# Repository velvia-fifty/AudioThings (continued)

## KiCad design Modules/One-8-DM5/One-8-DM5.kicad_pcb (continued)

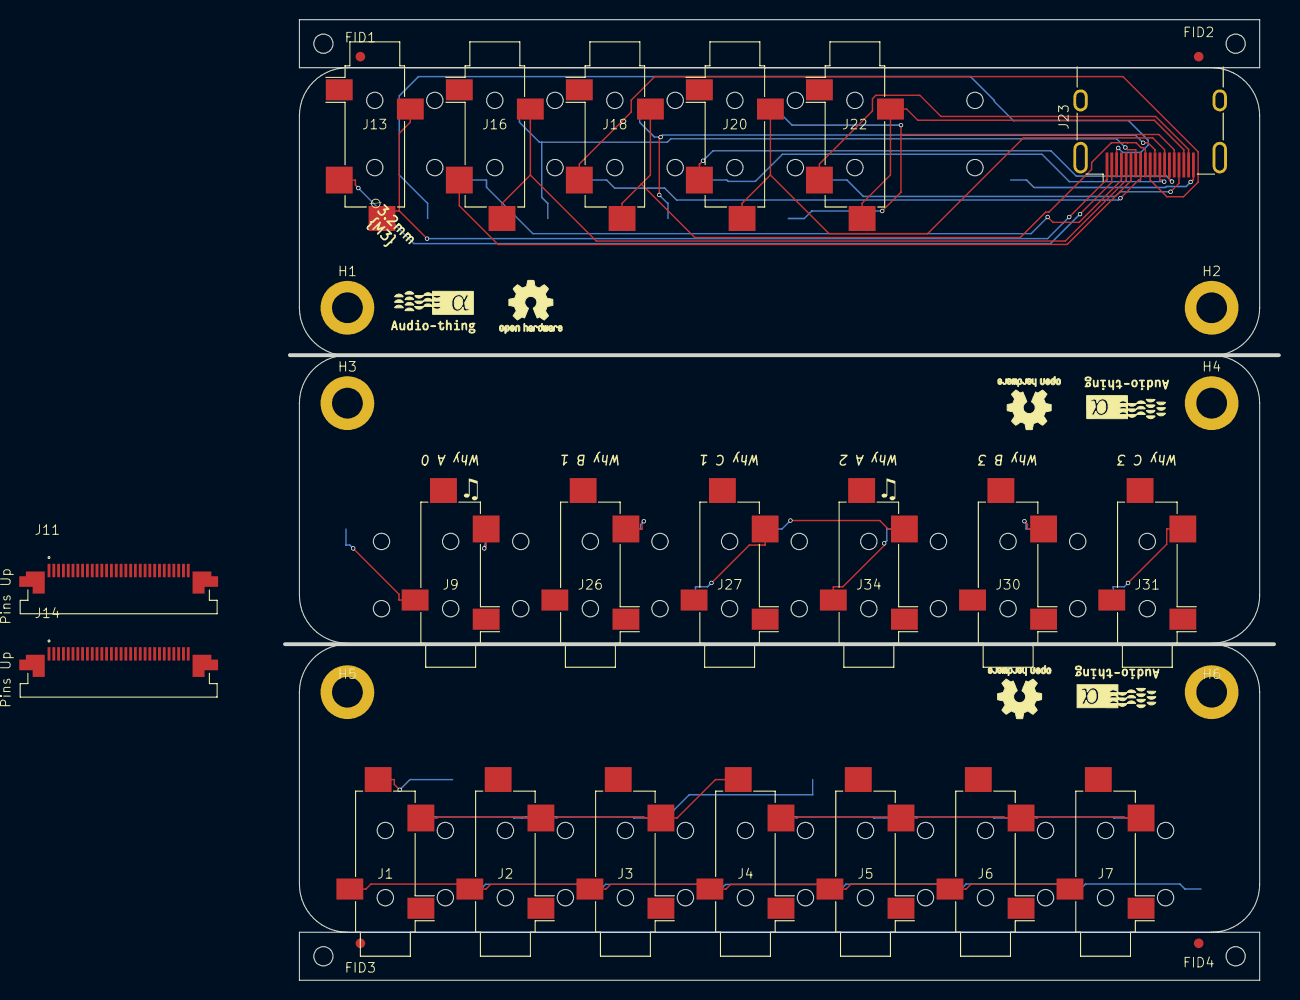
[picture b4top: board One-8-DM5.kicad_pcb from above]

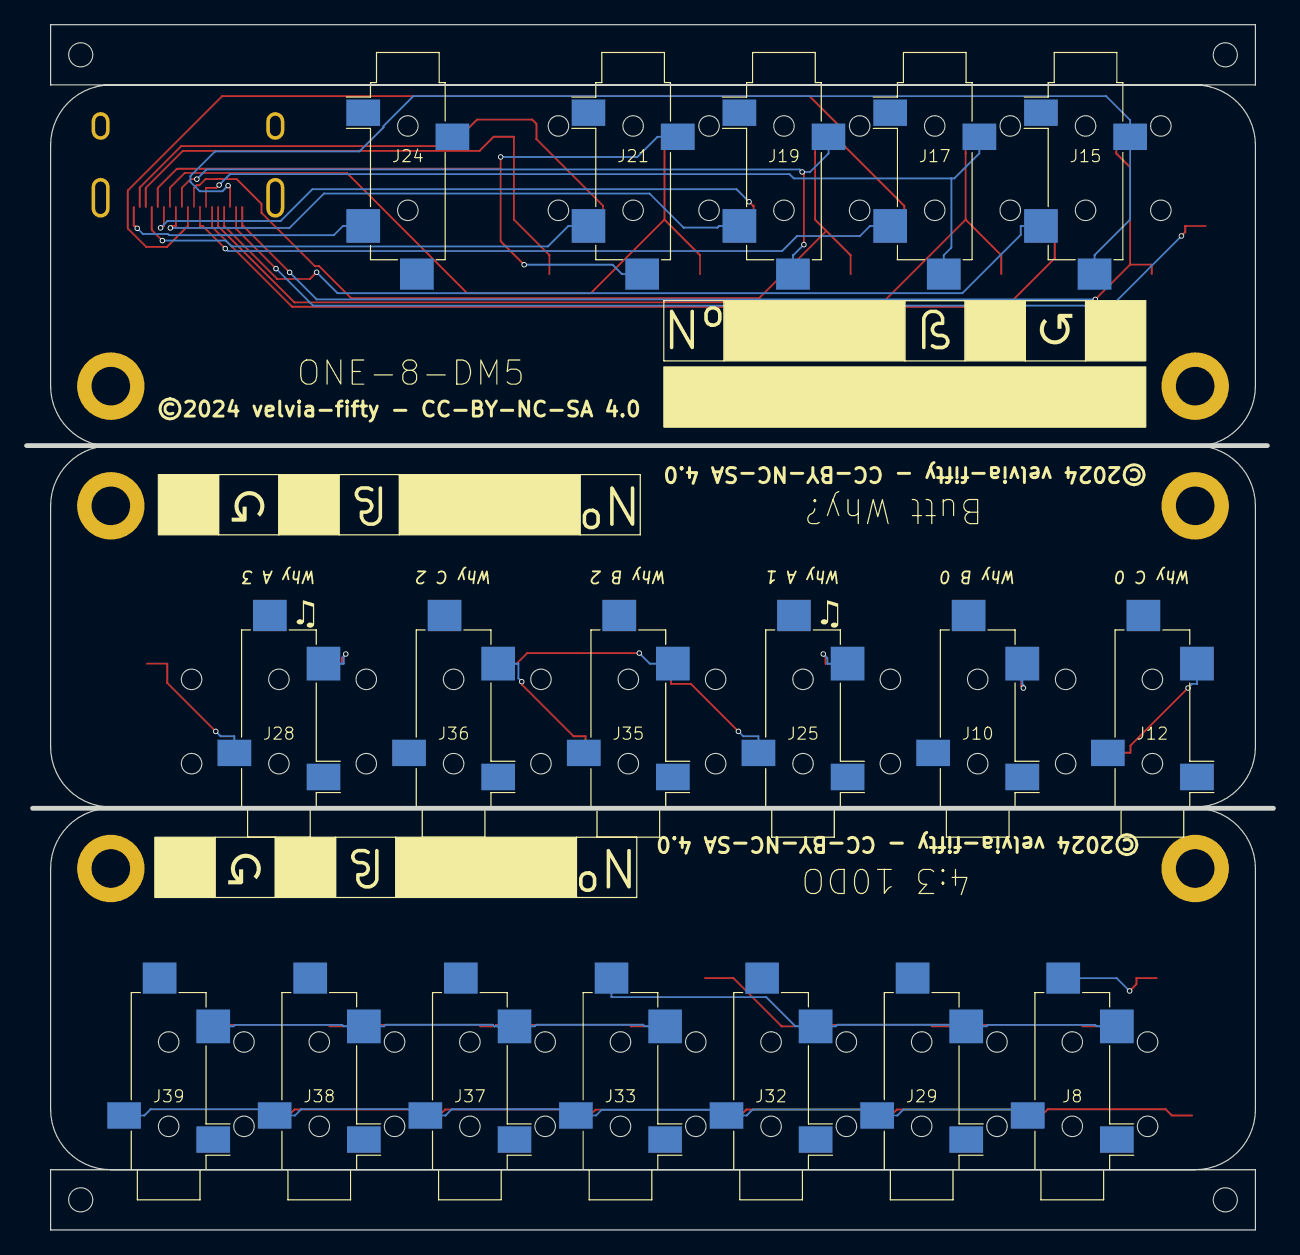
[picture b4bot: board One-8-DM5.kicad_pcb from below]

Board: 2 copper layers, 100.0 x 90.0 mm, 59 parts (18 on the bottom side), 35 nets.

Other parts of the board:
G1, G3, G5: LOGO; at-logo
G2, G4, G6: OSHW-Logo2_7.3x6mm_SilkScreen

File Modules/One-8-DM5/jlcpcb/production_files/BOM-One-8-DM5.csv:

Comment,Designator,Footprint,LCSC,Quantity
ALPHA,J1,Jack_3.5mm_CUI_SJ-3524-SMT_Horizontal,C22359753,1
HDMI,J23,HDMI_A_Molex_208658-1001_Horizontal,C916313,1
Why B 0,"J10,J12,J13,J15,J16,J17,J18,J19,J2,J20,J21,J22,J24,J25,J26,J27,J28,J29,J3,J30,J31,J32,J33,J34,J35,J36,J37,J38,J39,J4,J5,J6,J7,J8,J9",Jack_3.5mm_CUI_SJ-3524-SMT_Horizontal,C9900037324,35
